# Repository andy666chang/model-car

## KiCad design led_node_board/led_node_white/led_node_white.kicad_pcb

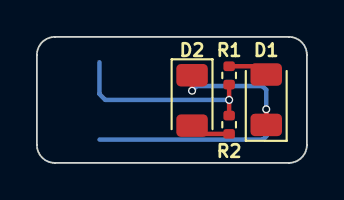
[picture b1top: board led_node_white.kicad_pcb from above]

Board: 2 copper layers, 15.0 x 7.0 mm, 5 parts (1 on the bottom side), 4 nets.

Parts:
+: Conn_01x02; SolderJumper-2_P1.3mm_Open_Pad1.0x1.5mm
D1, D2: LED; LED_1206_3216Metric
R1, R2: R; R_0402_1005Metric

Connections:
+3.3V: +.1, R1.2, R2.2
GND: +.2, D1.1 (K), D2.1 (K)
unnamed: D1.2 (A), R1.1
unnamed: D2.2 (A), R2.1

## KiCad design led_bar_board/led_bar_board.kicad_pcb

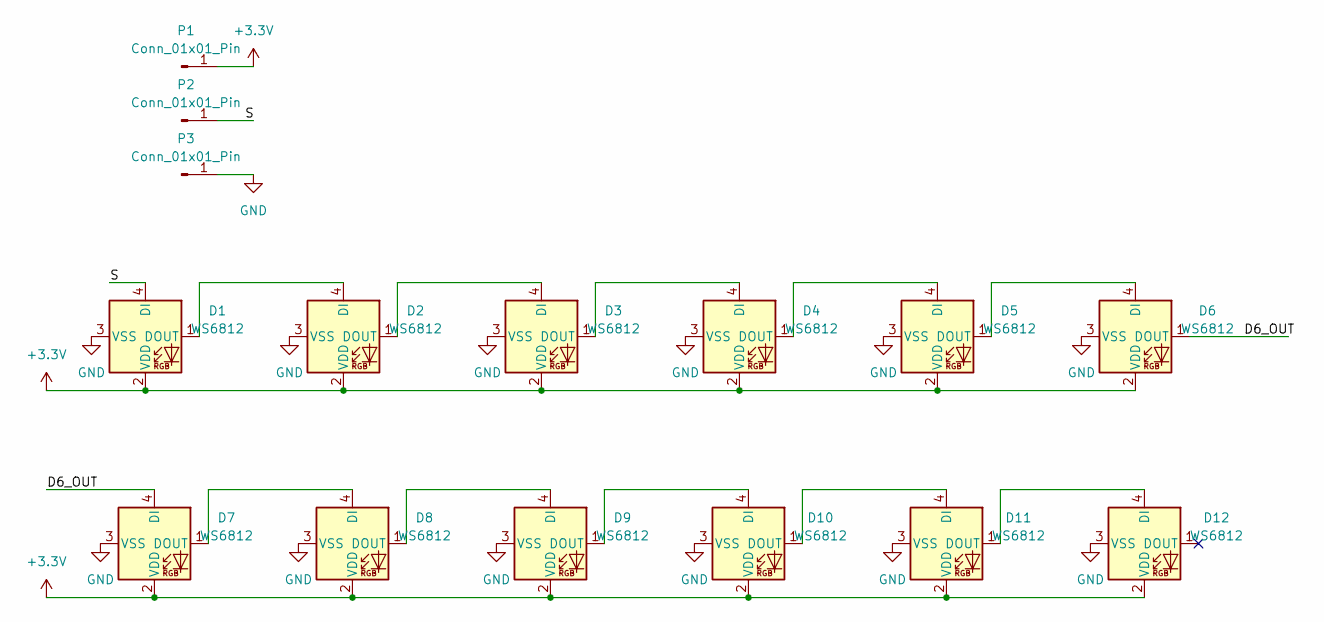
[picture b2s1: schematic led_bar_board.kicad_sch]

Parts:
D1, D2, D3, D4, D5, D6, D7, D8, D9, D10, D11, D12: WS6812; LED_SK6812_EC15_1.5x1.5mm; JLCPCB C5349953 / C41347988
P1, P2, P3: Conn_01x01_Pin

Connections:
+3.3V: D1.2 (VDD), D2.2 (VDD), D3.2 (VDD), D4.2 (VDD), D5.2 (VDD), D6.2 (VDD), D7.2 (VDD), D8.2 (VDD), D9.2 (VDD), D10.2 (VDD), D11.2 (VDD), D12.2 (VDD), P1.1
/D6_OUT: D6.1 (DOUT), D7.4 (DI)
/S: D1.4 (DI), P2.1
GND: D1.3 (VSS), D2.3 (VSS), D3.3 (VSS), D4.3 (VSS), D5.3 (VSS), D6.3 (VSS), D7.3 (VSS), D8.3 (VSS), D9.3 (VSS), D10.3 (VSS), D11.3 (VSS), D12.3 (VSS), P3.1
unnamed: D1.1 (DOUT), D2.4 (DI)
unnamed: D2.1 (DOUT), D3.4 (DI)
unnamed: D3.1 (DOUT), D4.4 (DI)
unnamed: D4.1 (DOUT), D5.4 (DI)
unnamed: D5.1 (DOUT), D6.4 (DI)
unnamed: D7.1 (DOUT), D8.4 (DI)
unnamed: D8.1 (DOUT), D9.4 (DI)
unnamed: D9.1 (DOUT), D10.4 (DI)
unnamed: D10.1 (DOUT), D11.4 (DI)
unnamed: D11.1 (DOUT), D12.4 (DI)

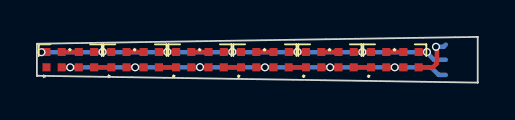
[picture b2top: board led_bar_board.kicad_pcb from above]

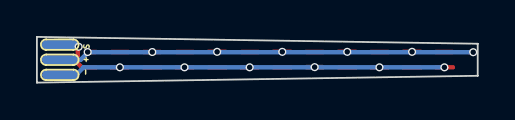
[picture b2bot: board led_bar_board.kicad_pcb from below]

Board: 2 copper layers, 24.5 x 2.5 mm, 15 parts (3 on the bottom side), 14 nets.

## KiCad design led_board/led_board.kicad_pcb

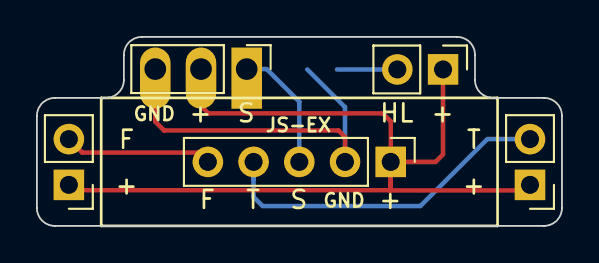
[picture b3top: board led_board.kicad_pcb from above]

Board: 2 copper layers, 29.2 x 10.5 mm, 6 parts (1 on the bottom side), 6 nets.

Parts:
J1: Conn_01x03; PinHeader_1x03_P2.54mm_Vertical
J2, J3, J4: Conn_01x02; PinHeader_1x02_P2.54mm_Vertical
JSB1: Conn_01x05; PinHeader_1x05_P2.54mm_Vertical
R1: R; R_0603_1608Metric

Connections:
+3.3V: J1.2, J2.1, J3.1, J4.1, JSB1.1
/F: J3.2, JSB1.5
/HL: J2.2, R1.1
/S: J1.1, JSB1.3
/T: J4.2, JSB1.4
GND: J1.3, JSB1.2, R1.2

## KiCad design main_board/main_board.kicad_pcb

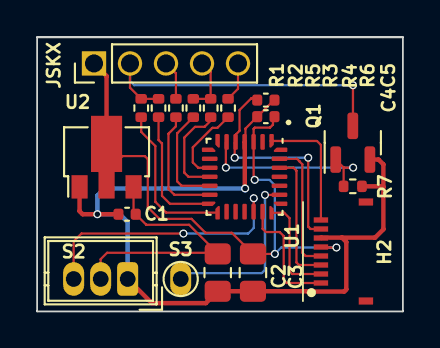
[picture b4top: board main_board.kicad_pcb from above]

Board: 2 copper layers, 20.3 x 15.2 mm, 19 parts (0 on the bottom side), 22 nets.

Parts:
C1, C4, C5: 100n; C_0402_1005Metric
C2, C3: 10u; C_0805_2012Metric_Pad1.18x1.45mm_HandSolder
H2: Conn_01x08; TE_0-1734839-8_1x08-1MP_P0.5mm_Horizontal
JSKX: Conn_01x05; PinHeader_1x05_P2.00mm_Vertical
Q1: NMOS; SOT-23
R1: 680; R_0402_1005Metric
R2, R4, R6: 0; R_0402_1005Metric
R3: 220; R_0402_1005Metric
R5, R7: 100; R_0402_1005Metric
S2: Conn_01x03; Wuerth_WR-WTB_64800311622_1x03_P1.50mm_Vertical
S3: Conn_01x01; TestPoint_THTPad_D1.5mm_Drill0.7mm
U1: STM32G031G8Ux; QFN-28_4x4mm_P0.5mm
U2: AMS1117-3.3; SOT-89-3

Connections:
+5V: C1.1, C2.1, S2.2, U2.3 (VI)
/CHASSIS: R5.1, U1.13 (PA7)
/FIRE: R6.1, U1.10 (PA4)
/HEAD_0: R1.1, U1.15 (PB1)
/HEAD_1: R2.1, U1.14 (PB0)
/LED_CHASSIS: JSKX.3, R5.2
/LED_FIRE: JSKX.5, R6.2
/LED_HEAD: JSKX.2, Q1.3 (D), R1.2, R2.2
/LED_TAIL: JSKX.4, R3.2, R4.2
/RST: C5.1, H2.7, U1.5 (PF2)
/SG_BT: S3.1, U1.23 (PB3)
/SG_THRO: S2.3, U1.19 (PA12/PA10)
/SW: Q1.1 (G), R7.1, U1.6 (PA0)
/SWCLK: H2.2, U1.21 (PA14)
/SWDIO: H2.1, U1.20 (PA13)
/TAIL_0: R3.1, U1.12 (PA6)
/TAIL_1: R4.1, U1.11 (PA5)
/TP1: H2.8, U1.1 (PC14)
/UART_RX: H2.4, U1.27 (PB7)
/UART_TX: H2.3, U1.26 (PB6)
/VCC: C3.1, C4.1, H2.5, JSKX.1, U1.3 (VDD), U2.2 (VO)
GND: C1.2, C2.2, C3.2, C4.2, C5.2, H2.6, Q1.2 (S), R7.2, S2.1, U1.4 (VSS), U2.1 (GND)

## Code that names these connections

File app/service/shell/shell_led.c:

#include <stdio.h>
#include <stdlib.h>
#include <string.h>
#include <stdint.h>
#include <stdbool.h>
#include <errno.h>

#include <module/shell.h>
#include <module/log.h>

#include "interface/interface.h"
#include <interface/led.h>

#define TAG "SHELL-LED"

static int shell_led(int argc, char *argv[]) {
    int idx = 99, level = 99;

    for (int i = 0; i < argc; i++) {
        if ( !strcmp(argv[i], "-i") && (i+1) < argc) {
            idx = strtol(argv[i+1], NULL, 10);
            continue;
        }

        if ( !strcmp(argv[i], "-l") && (i+1) < argc) {
            level = (bool)strtol(argv[i+1], NULL, 10);
            continue;
        }
    }

    LOGI(TAG,"idx: %d, level: %d", idx, level);

    switch (idx) {
        case 0:
            LOGI(TAG, "HEAD_0_Pin level: %d", level);
            led_set(LED_HEAD_0, level);
            break;
        
        case 1:
            LOGI(TAG, "HEAD_1_Pin level: %d", level);
            led_set(LED_HEAD_1, level);
            break;

        case 2:
            LOGI(TAG, "CHASIS_Pin level: %d", level);
            led_set(LED_CHASIS, level);
            break;

        case 3:
            LOGI(TAG, "TAIL_0_Pin level: %d", level);
            led_set(LED_TAIL_0, level);
            break;

        case 4:
            LOGI(TAG, "TAIL_1_Pin level: %d", level);
            led_set(LED_TAIL_1, level);
            break;

        case 5:
            LOGI(TAG, "FIRE_Pin level: %d", level);
            led_set(LED_FIRE, level);
            break;
        
        default:
            LOGE(TAG,"Unknow LED: %d", idx);
            break;
    }

    return 0;
}

#include <zephyr/kernel.h>

STRUCT_SECTION_ITERABLE(shell_t, led) = {
    .name = "led",
    .info = "led -i <0...5> -l <0...1>",
    .func = shell_led,
    .sub = NULL,
};

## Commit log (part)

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2023-11-18 feat: init project
2023-11-18 feat(ref): add ref picture
2023-11-18 feat(main_board): add component for temp
2023-11-18 fix(main_board): fix footprint
2023-11-23 feat(main_board): connect net
2024-11-06 feat(board/mcu): change mcu to sn32f805
2024-11-19 feat(board/mcu): change mcu to STM32G031G8U8
2024-11-23 feat(board): update ohm
2024-11-23 feat(board): update JLC part number and gerber
2024-12-23 feat(board): create led board
2024-12-24 feat(board): modify board outline
2024-12-24 feat(board): release led_board gerber
2024-12-24 feat(main_board): modify placement
2024-12-24 feat(main_board): update jlcpcb part number
2024-12-24 feat(main_board): release main_board gerber
2024-12-24 feat(tail_board): create tail board
2024-12-24 feat(tail_board): release tail_board gerber
2025-10-28 feat(main_board/led): modify ohm for led
2025-11-14 feat(main_board/led): add MOSFET for led bar
2025-11-15 feat(main_board/led): 高release gerber
2025-11-22 feat(led_bar): create board
2025-12-24 feat: init env
2025-12-24 feat(board): create board
2025-12-24 feat(app): create app
2025-12-24 feat(flash): modify flash partition
2025-12-24 feat(app): remove thread control
2025-12-25 feat(rc): get rc duty by timer and GPIO
2025-12-25 feat(led): implment led control
2025-12-25 feat(flash): implment flash control for saving config
2025-12-25 feat(uuid): read chip uuid
2025-12-25 feat(btn): imlement btn service
2025-12-25 feat(btn): imlement thro service
2025-12-25 fix(led): modify head led in dts
2025-12-25 fix(time): add sleep time for rc stable
2025-12-25 feat(led_bar): add led_bar support
2025-12-27 feat(rc): modify rc capture by pwm
2025-12-29 refactor: refine timeout by marco
2025-12-29 feat(log): port tiny log module
2025-12-29 feat(crc): implement crc32 for config data
2025-12-30 feat(led_bar): update led component
2025-12-30 feat: modify logo
2025-12-31 fix(break): modify break entry logic
2025-12-31 feat: refine logic
2025-12-31 feat(btn): refine flash log
2025-12-31 feat(shell): port shell
2026-01-01 refactor(shell): refine shell by section map
2026-01-01 feat(thread): implement multithread service
2026-01-01 refactor(thread): replace memory pool for fifo
    CONFIG_MULTITHREADING=n
    ```
    Memory region Used Size Region Size %age Used
    FLASH: 31944 B 60 KB 51.99%
    RAM: 3136 B 8 KB 38.28%
    IDT_LIST: 0 GB 32 KB 0.00%
2026-01-23 feat(led_board): modify hole size
2026-01-26 feat(led_bar): modify shape and pad
2026-01-26 feat(led_board): update array
2026-05-30 feat(driver): sepaerate driver for qemu
